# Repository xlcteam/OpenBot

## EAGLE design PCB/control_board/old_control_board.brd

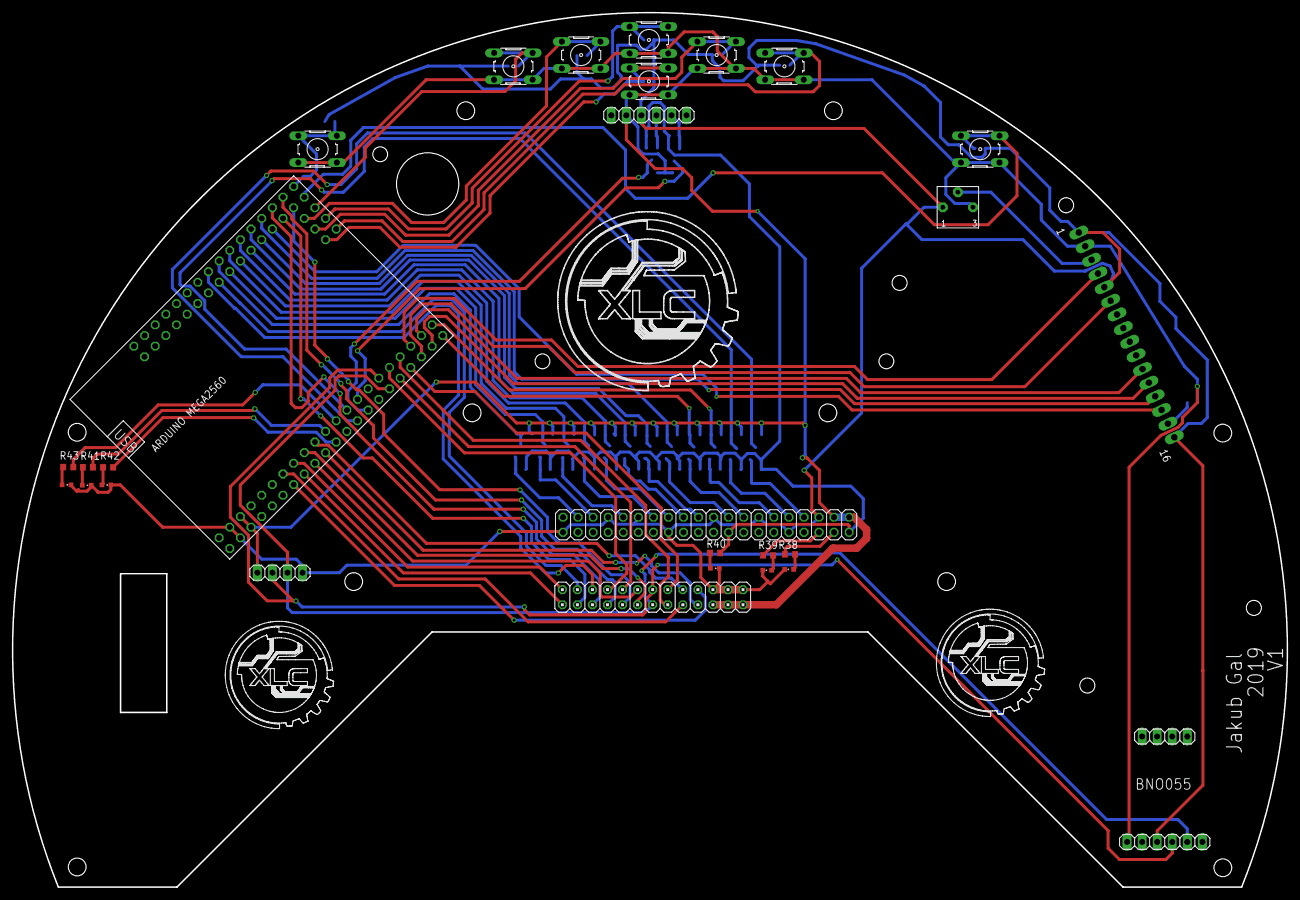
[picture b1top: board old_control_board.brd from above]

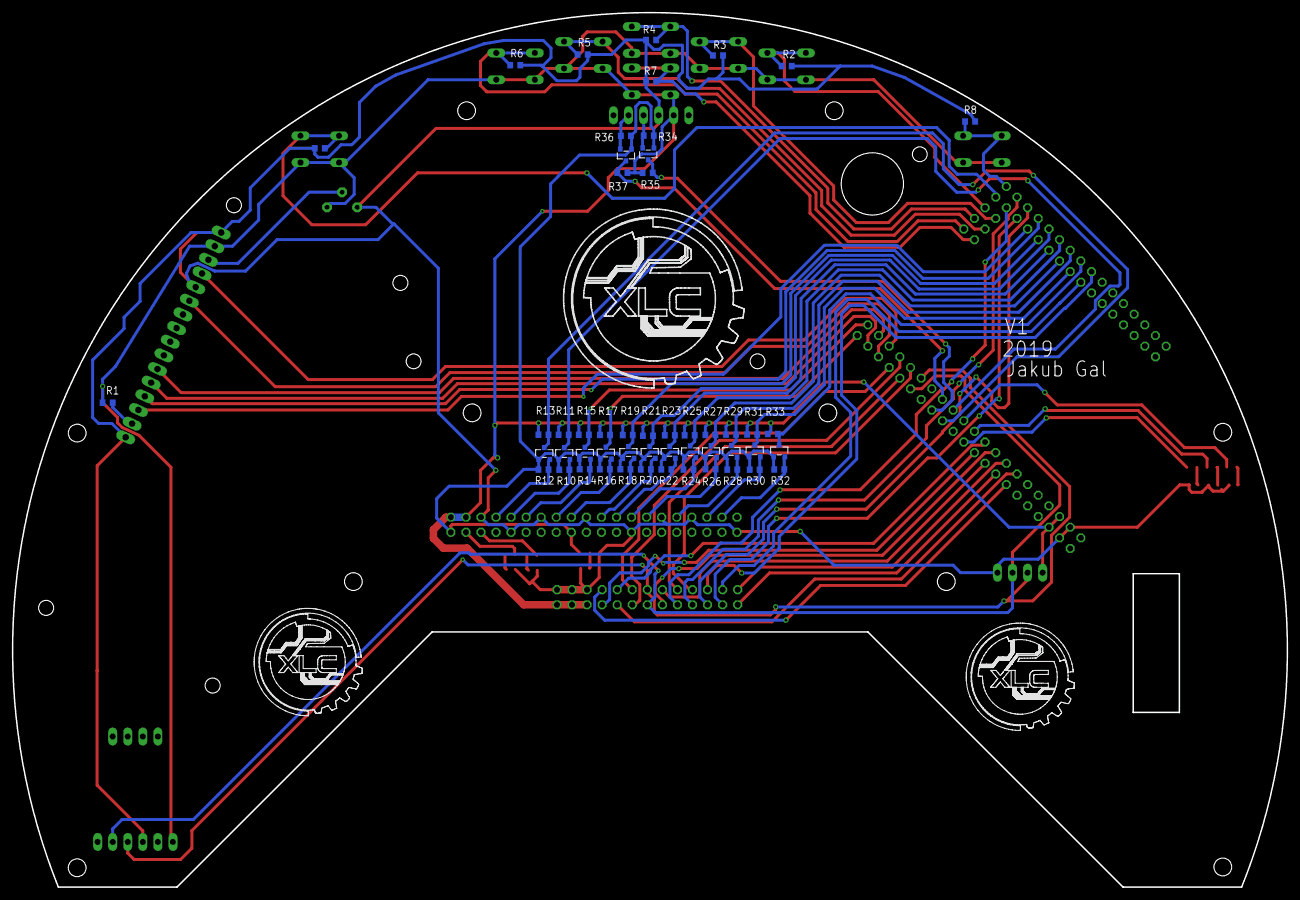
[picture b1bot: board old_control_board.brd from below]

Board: 2 copper layers, 215.0 x 147.5 mm, 79 parts (51 on the bottom side), 78 nets.

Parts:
DIS1: LCD_DISPLEJ_16X2
JP1: 2X13
JP2: 2X20
JP3: 1X04
JP4: 1X06
LED1, LED2, LED3, LED4, LED5, LED6: LEDCHIPLED_0603; CHIPLED_0603
Q1, Q2, Q3, Q4, Q5, Q6, Q7, Q8, Q9, Q10, Q11, Q12, Q13, Q14: BSS138; SOT23
R1, R38, R39, R41, R42, R43: 220R; R0603
R2, R3, R4, R5, R6, R7, R8, R9, R10, R11, R12, R13, R14, R15, R16, R17, R18, R19, R20, R21, R22, R23, R24, R25, R26, R27, R28, R29, R30, R31, R32, R33, R34, R35, R36, R37: 10K; R0603
R40: 330R; R0603
R45: 3362P
S1, S2, S3, S4, S5, S6, S7, S8: B3F-10XX
U$1: MEGA2560_MIKRO
U$2: BNO055; BNO005

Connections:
3V: JP2.23, JP2.39, Q1.1, Q2.1, Q3.1, Q4.1, Q5.1, Q6.1, Q7.1, Q8.1, Q9.1, Q10.1, Q11.1, Q12.1, Q13.1, Q14.1, R10.1, R12.1, R14.1, R16.1, R18.1, R20.1, R22.1, R24.1, R26.1, R28.1, R30.1, R32.1, R34.1, R36.1, R40.2
5V: DIS1.2, JP1.21, JP1.23, JP1.25, JP2.38, JP2.40, JP3.1, JP4.5, R1.1, R11.1, R13.1, R15.1, R17.1, R19.1, R21.1, R23.1, R25.1, R27.1, R29.1, R31.1, R33.1, R35.1, R37.1, R45.3, S1.3, S1.4, S2.3, S2.4, S3.3, S3.4, S4.3, S4.4, S5.3, S5.4, S6.3, S6.4, S7.3, S7.4, S8.3, S8.4, U$1.+5V.1, U$1.+5V.2, U$2.VIN
BUTON_1: R2.1, S1.1, S1.2, U$1.D48
BUTON_2: R3.1, S2.1, S2.2, U$1.D49
BUTON_3: R4.1, S3.1, S3.2, U$1.D50
BUTON_4: R5.1, S4.1, S4.2, U$1.D51
BUTON_5: R6.1, S5.1, S5.2, U$1.D52
BUTON_6: R7.1, S6.1, S6.2, U$1.D53
BUTON_7: R8.1, S7.1, S7.2, U$1.D46
BUTON_8: R9.1, S8.1, S8.2, U$1.D47
DB4: DIS1.11, U$1.D28
DB5: DIS1.12, U$1.D29
DB6: DIS1.13, U$1.D40
DB7: DIS1.14, U$1.D41
DRIBLER_A: JP1.16, U$1.D25
DRIBLER_B: JP1.15, U$1.D24
DRIBLER_PWM: JP1.18, U$1.D8
DRIBLER_SIGNAL: JP1.17, U$1.D2
GND: DIS1.1, DIS1.5, DIS1.16, JP1.22, JP1.24, JP1.26, JP2.1, JP2.8, JP2.12, JP2.15, JP2.22, JP2.28, JP2.31, JP2.36, JP3.4, JP4.4, LED1.C, LED2.C, LED3.C, LED4.C, LED5.C, LED6.C, R2.2, R3.2, R4.2, R5.2, R6.2, R7.2, R8.2, R9.2, R45.1, U$1.GND.1, U$1.GND.2, U$2.GND
KICK: JP1.19, U$1.D9
LINE_INTERUPT: JP1.20, U$1.D3
MOTOR_A_A_1: JP1.6, U$1.A14
MOTOR_A_A_2: JP1.7, U$1.D44
MOTOR_A_B_1: JP1.4, U$1.A15
MOTOR_A_B_2: JP1.9, U$1.D45
MOTOR_A_PWM_1: JP1.2, U$1.D4
MOTOR_A_PWM_2: JP1.11, U$1.D6
MOTOR_B_A_1: JP1.5, U$1.D42
MOTOR_B_A_2: JP1.8, U$1.D22
MOTOR_B_B_1: JP1.3, U$1.D43
MOTOR_B_B_2: JP1.10, U$1.D23
MOTOR_B_PWM_1: JP1.1, U$1.D5
MOTOR_B_PWM_2: JP1.12, U$1.D7
unnamed: JP2.37, R38.2
unnamed: DIS1.15, R1.2
unnamed: DIS1.3, R45.2
unnamed: LED2.A, R39.1
unnamed: JP2.35, R39.2
unnamed: LED3.A, R40.1
unnamed: LED4.A, R41.1
unnamed: R41.2, U$1.D10
unnamed: LED5.A, R42.1
unnamed: R42.2, U$1.D11
unnamed: LED6.A, R43.1
unnamed: R43.2, U$1.D12
unnamed: LED1.A, R38.1
RN: DIS1.6, U$1.D27
RPI_D1_3V: JP2.30, Q3.2, R14.2
RPI_D1_5V: Q3.3, R15.2, U$1.D30
RPI_D2_3V: JP2.26, Q4.2, R16.2
RPI_D2_5V: Q4.3, R17.2, U$1.D31
RPI_D3_3V: JP2.24, Q5.2, R18.2
RPI_D3_5V: Q5.3, R19.2, U$1.D39
RPI_D4_3V: JP2.20, Q6.2, R20.2
RPI_D4_5V: Q6.3, R21.2, U$1.D38
RPI_D5_3V: JP2.18, Q7.2, R22.2
RPI_D5_5V: Q7.3, R23.2, U$1.D37
RPI_D6_3V: JP2.16, Q8.2, R24.2
RPI_D6_5V: Q8.3, R25.2, U$1.D36
RPI_D7_3V: JP2.14, Q9.2, R26.2
RPI_D7_5V: Q9.3, R27.2, U$1.D35
RPI_D8_3V: JP2.10, Q10.2, R28.2
RPI_D8_5V: Q10.3, R29.2, U$1.D34
RPI_D9_3V: JP2.6, Q11.2, R30.2
RPI_D9_5V: Q11.3, R31.2, U$1.D33
RPI_D10_3V: JP2.4, Q12.2, R32.2
RPI_D10_5V: Q12.3, R33.2, U$1.D32
RPI_RX_3V: JP2.32, Q1.2, R10.2
RPI_RX_5V: Q1.3, R11.2, U$1.D14
RPI_TX_3V: JP2.34, Q2.2, R12.2
RPI_TX_5V: Q2.3, R13.2, U$1.D15
RS: DIS1.4, U$1.D26
RX_BLU_3V: JP4.2, Q14.2, R36.2
RX_BLU_5V: Q14.3, R37.2, U$1.D16
SCL: JP1.13, JP3.3, U$1.D21, U$2.SCL
SDA: JP1.14, JP3.2, U$1.D20, U$2.SDA
TX_BLU_3V: JP4.3, Q13.2, R34.2
TX_BLU_5V: Q13.3, R35.2, U$1.D17

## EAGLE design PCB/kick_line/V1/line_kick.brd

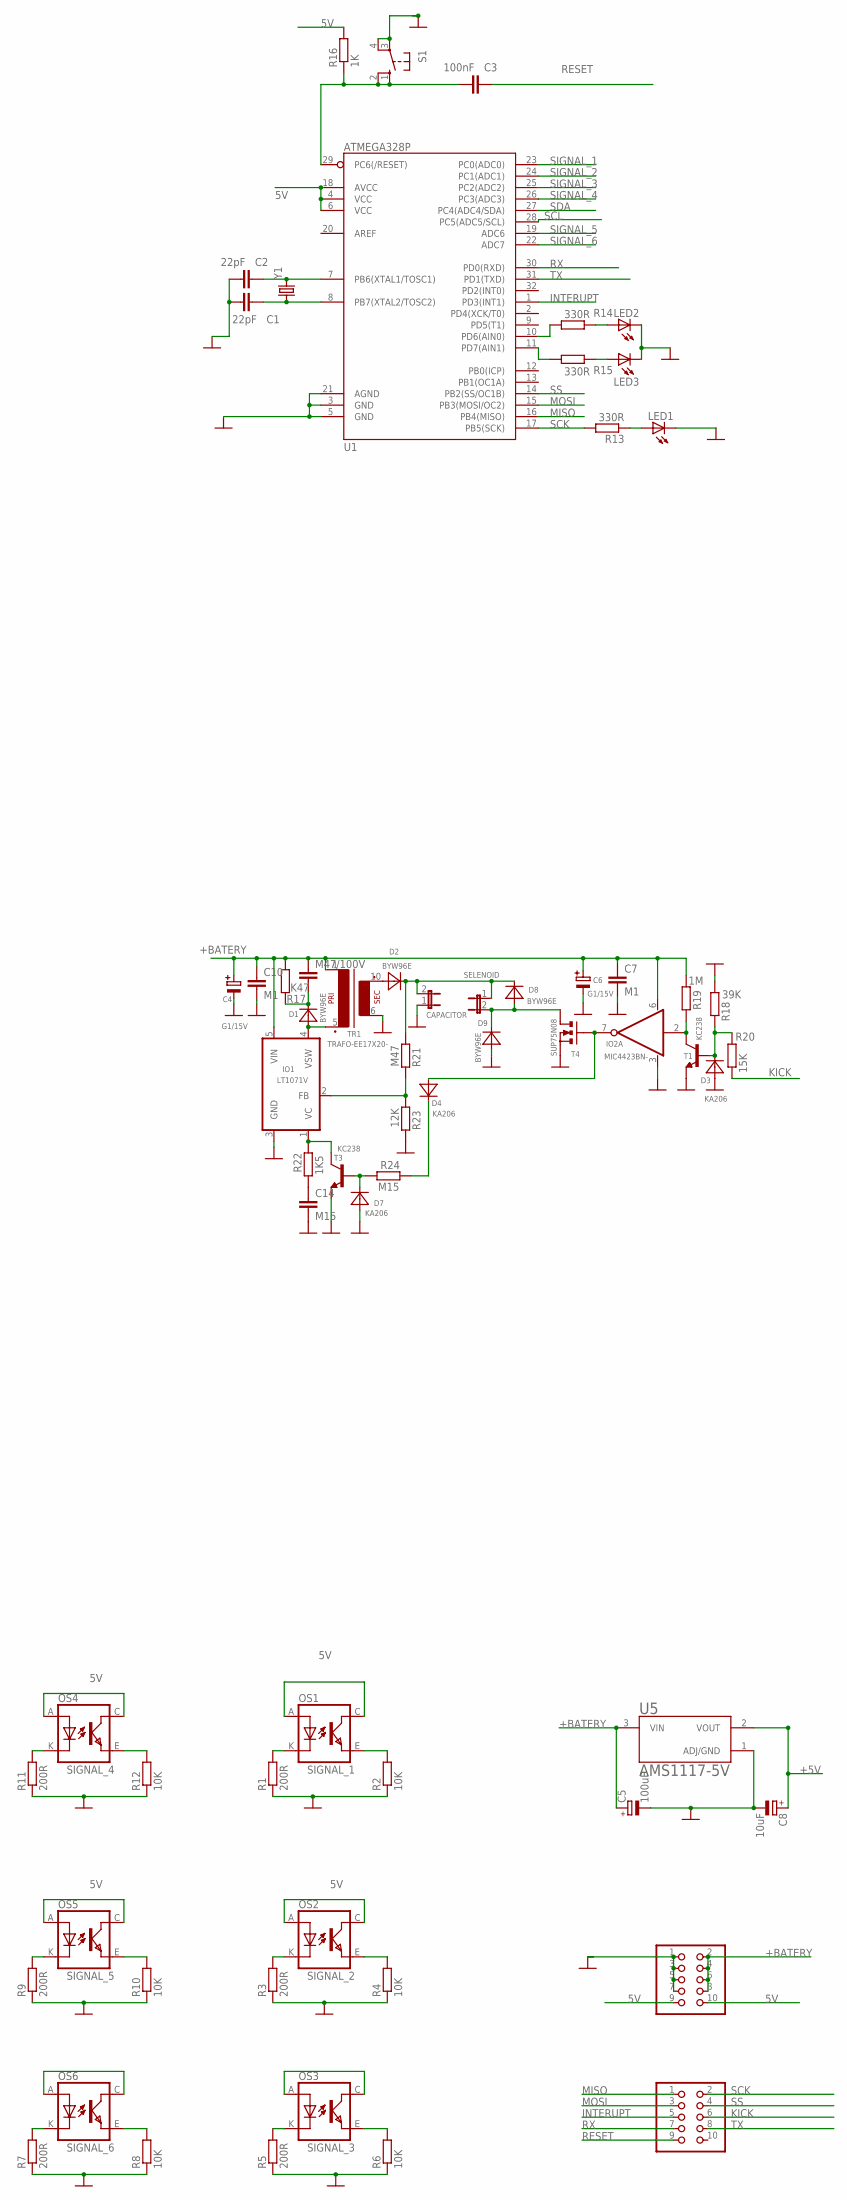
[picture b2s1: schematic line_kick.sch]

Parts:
C1, C2: 22pF; C0603
C3: 100nF; C0603
C4, C6: G1/15V; E-2,5/7-RAD
C5: 100uF; UD-6,3X7,7_NICHICON
C7, C10: M1; C0805K
C8: 10uF; UD-4X5,8_NICHICON
C14: M15; C0805K
CAPACITOR: JP2EN; JP2E
D1, D2, D8, D9: BYW96E; D-10
D3, D4, D7: KA206; D-7,5
IO1: LT1071V; TO-220-5P
IO2: MIC4423BN-; DIL8
JP2, JP3: PINHD-2X5; 2X05
LED1, LED2, LED3: LEDCHIPLED_0603; CHIPLED_0603
M47/100V: C-EUC0805K; C0805K
OS1, OS2, OS3, OS4, OS5, OS6: TCRT5000
R1, R3, R5, R7, R9, R11: 200R; R0603
R2, R4, R6, R8, R10, R12: 10K; R0603
R13, R14, R15: 330R; R0603
R16: 1K; R0603
R17: K47; R0603
R18: 39K; R0603
R19: 1M; R0603
R20: 15K; R0603
R21: M47; R0603
R22: 1K5; R0603
R23: 12K; R0603
R24: M15; R0603
S1: 10-XX; B3F-10XX
SELENOID: JP2EN; JP2E
T1, T3: KC238; TO-92
T4: SUP75N08; TO-220
TR1: TRAFO-EE17X20-; TRAFO-EE17X20
U1: ATMEGA328P; TQFP32-08
U5: AMS1117-5V; SOT229P700X180-4N
Y1: CRYSTALHC49US; HC49US

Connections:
5V: JP3.9, JP3.10, OS1.A (ANODE), OS1.C (COLLECTOR), OS2.A (ANODE), OS2.C (COLLECTOR), OS3.A (ANODE), OS3.C (COLLECTOR), OS4.A (ANODE), OS4.C (COLLECTOR), OS5.A (ANODE), OS5.C (COLLECTOR), OS6.A (ANODE), OS6.C (COLLECTOR), R16.2, U1.4 (VCC), U1.6 (VCC), U1.18 (AVCC)
+5V: C8.+, U5.2 (VOUT)
+BATERY: C4.+, C5.+, C6.+, C7.1, C10.1, IO1.5 (VIN), IO2.6 (VCC), JP3.2, JP3.4, JP3.6, JP3.8, M47/100V.1, R17.1, R19.2, TR1.1, U5.3 (VIN)
GND: C1.1, C2.1, C4.-, C5.-, C6.-, C7.2, C8.-, C10.2, C14.2, CAPACITOR.1, D3.A, D7.A, D9.A, IO1.3 (GND), IO2.3 (GND), JP3.1, JP3.3, JP3.5, JP3.7, LED1.C, LED2.C, LED3.C, R1.1, R2.1, R3.1, R4.1, R5.1, R6.1, R7.1, R8.1, R9.1, R10.1, R11.1, R12.1, R18.2, R23.1, S1.3, S1.4 (P1), T1.3 (E), T3.3 (E), T4.3 (S), TR1.6 (3), U1.3 (GND), U1.5 (GND), U1.21 (AGND), U5.1 (ADJ/GND)
INTERUPT: JP2.5, U1.1 (PD3(INT1))
KICK: JP2.6, R20.1
MISO: JP2.1, U1.16 (PB4(MISO))
MOSI: JP2.3, U1.15 (PB3(MOSI/OC2))
unnamed: OS1.K (CATHODE), R1.2
unnamed: OS2.K (CATHODE), R3.2
unnamed: OS3.K (CATHODE), R5.2
unnamed: OS6.K (CATHODE), R7.2
unnamed: OS5.K (CATHODE), R9.2
unnamed: OS4.K (CATHODE), R11.2
unnamed: C2.2, U1.7 (PB6(XTAL1/TOSC1)), Y1.2
unnamed: C1.2, U1.8 (PB7(XTAL2/TOSC2)), Y1.1
unnamed: IO1.1 (VC), R22.1, T3.1 (C)
unnamed: C14.1, R22.2
unnamed: D2.A, TR1.10 (4)
unnamed: CAPACITOR.2, D2.K, D8.K, R21.2, SELENOID.1
unnamed: IO1.2 (FB), R21.1, R23.2
unnamed: D7.K, R24.2, T3.2 (B)
unnamed: C3.1, R16.1, S1.1 (S), S1.2 (S1), U1.29 (PC6(/RESET))
unnamed: LED1.A, R13.1
unnamed: IO2.2 (I), R19.1, T1.1 (C)
unnamed: LED2.A, R14.1
unnamed: R15.2, U1.11 (PD7(AIN1))
unnamed: LED3.A, R15.1
unnamed: R14.2, U1.10 (PD6(AIN0))
unnamed: D1.A, IO1.4 (VSW), TR1.5 (2)
unnamed: D1.K, M47/100V.2, R17.2
unnamed: D4.A, IO2.7 (O), T4.1 (G)
unnamed: D8.A, D9.K, SELENOID.2, T4.2 (D)
unnamed: D4.K, R24.1
unnamed: D3.K, R18.1, R20.2, T1.2 (B)
RESET: C3.2, JP2.9
RX: JP2.7, U1.30 (PD0(RXD))
SCK: JP2.2, R13.2, U1.17 (PB5(SCK))
SCL: U1.28 (PC5(ADC5/SCL))
SDA: U1.27 (PC4(ADC4/SDA))
SIGNAL_1: OS1.E (EMITTER), R2.2, U1.23 (PC0(ADC0))
SIGNAL_2: OS2.E (EMITTER), R4.2, U1.24 (PC1(ADC1))
SIGNAL_3: OS3.E (EMITTER), R6.2, U1.25 (PC2(ADC2))
SIGNAL_4: OS4.E (EMITTER), R12.2, U1.26 (PC3(ADC3))
SIGNAL_5: OS5.E (EMITTER), R10.2, U1.19 (ADC6)
SIGNAL_6: OS6.E (EMITTER), R8.2, U1.22 (ADC7)
SS: JP2.4, U1.14 (PB2(SS/OC1B))
TX: JP2.8, U1.31 (PD1(TXD))

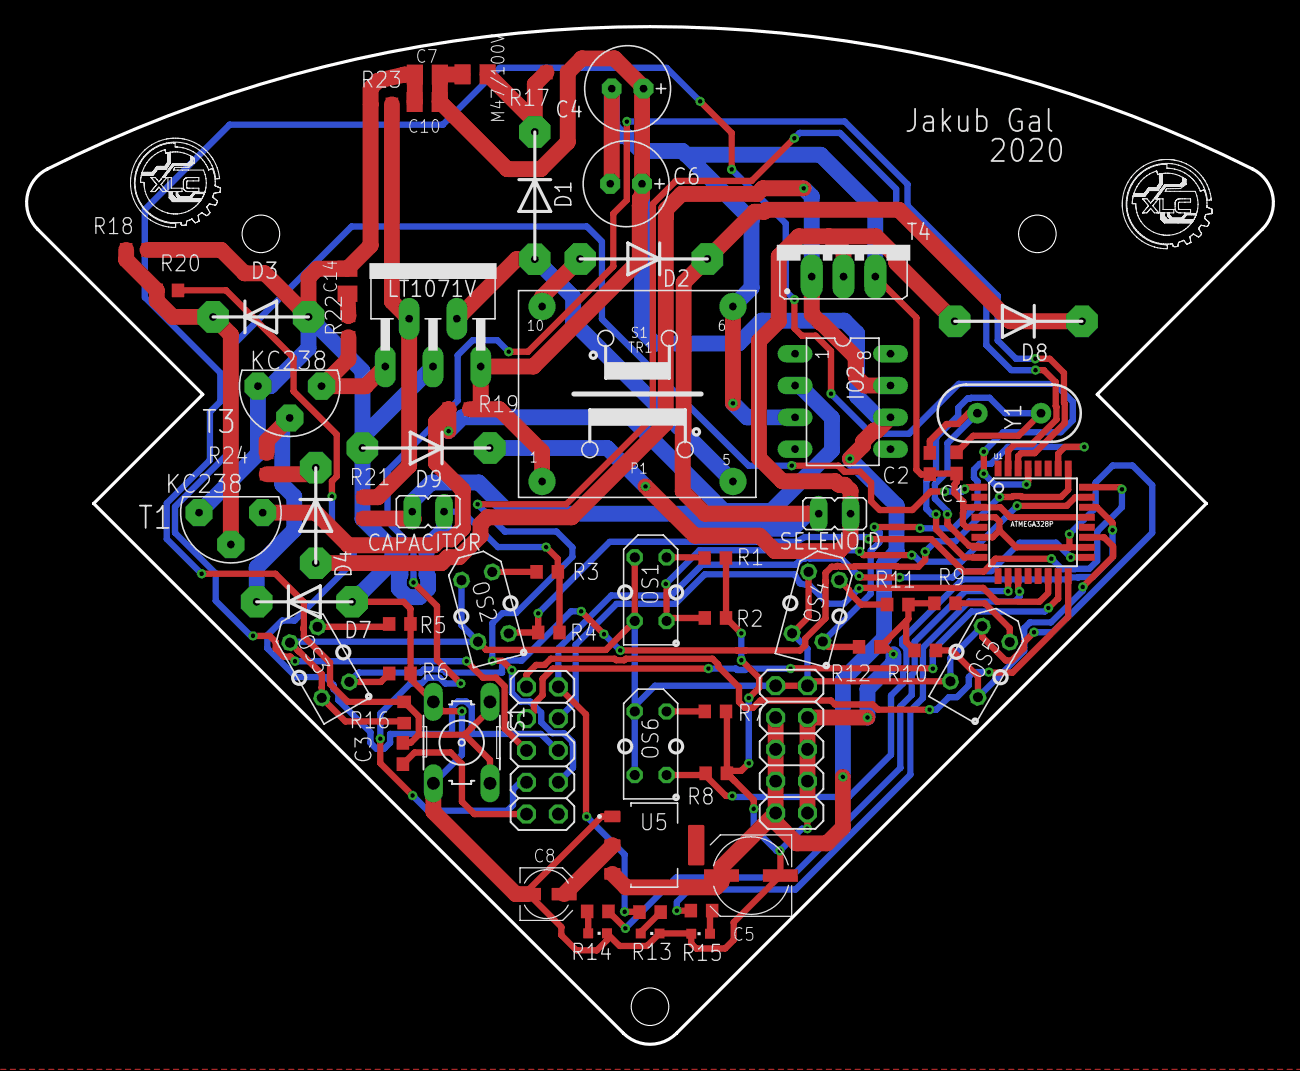
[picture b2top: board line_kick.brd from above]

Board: 2 copper layers, 99.5 x 81.3 mm, 65 parts (0 on the bottom side), 46 nets.

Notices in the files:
parts and their libraries:
SparkFun-DigitalIC: Licensing: CC v3.0 Share-Alike You are welcome to use this library for commercial purposes.
